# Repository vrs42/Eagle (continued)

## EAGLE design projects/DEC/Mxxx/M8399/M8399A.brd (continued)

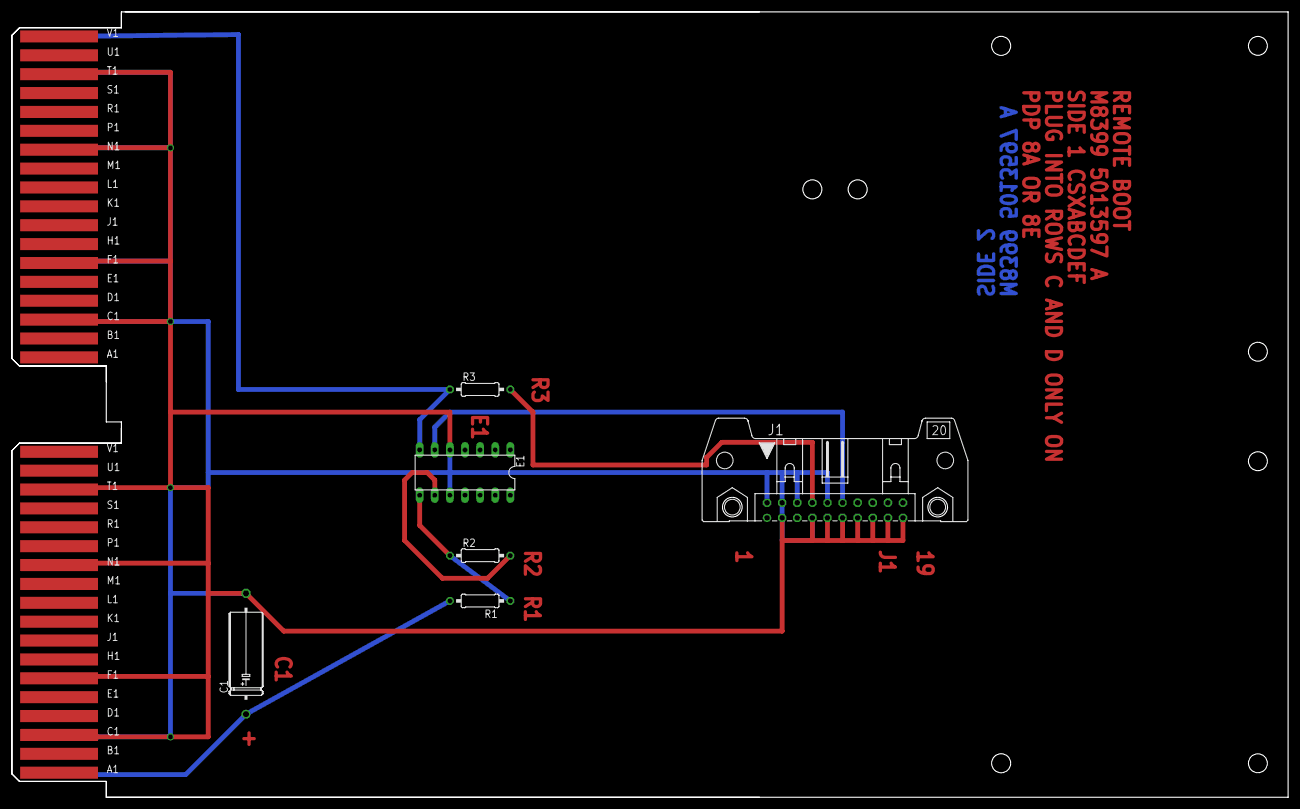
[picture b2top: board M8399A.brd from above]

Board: 2 copper layers, 214.6 x 132.1 mm, 9 parts (0 on the bottom side), 7 nets.

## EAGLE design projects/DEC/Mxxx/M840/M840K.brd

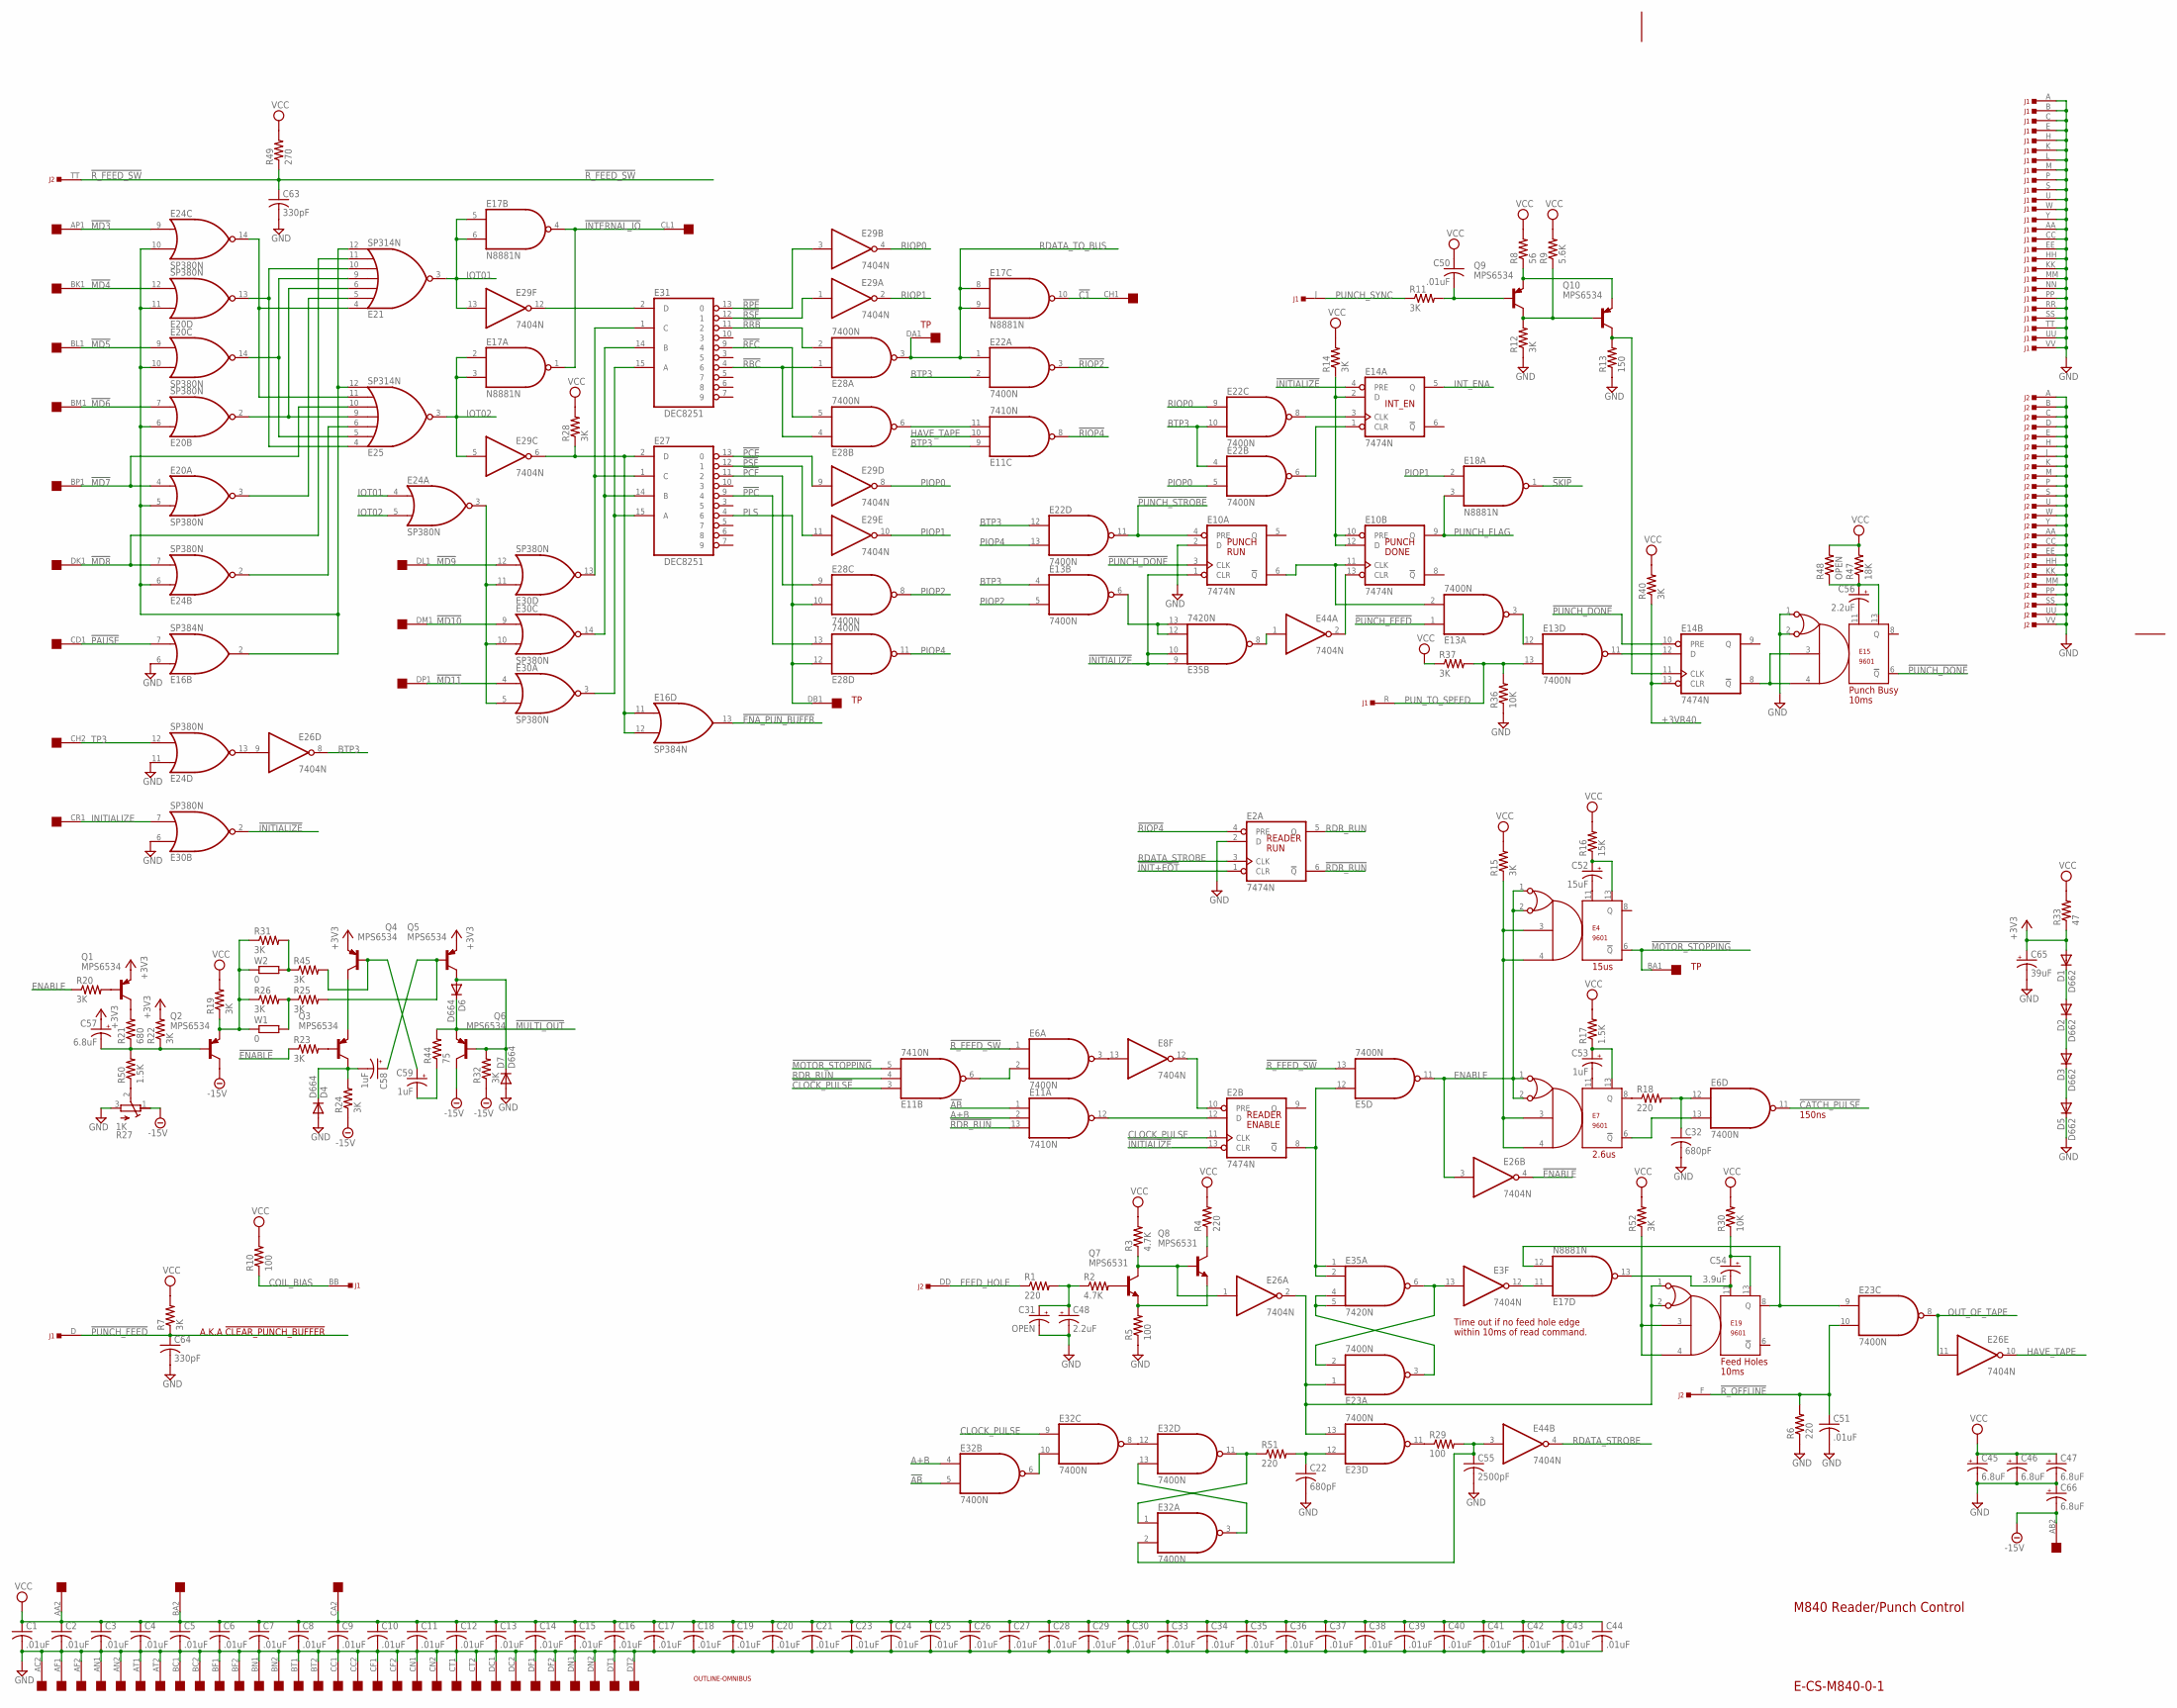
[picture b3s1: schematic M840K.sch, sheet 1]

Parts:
C1, C2, C3, C4, C5, C6, C7, C8, C9, C10, C11, C12, C13, C14, C15, C16, C17, C18, C19, C20, C21, C23, C24, C25, C26, C27, C28, C29, C30, C33, C34, C35, C36, C37, C38, C39, C40, C41, C42, C43, C44: .01uF; C063-025X075
C22, C32: 680pF; C063-025X075
C31: OPEN; E15-5
C45, C46, C47, C57, C66: 6.8uF; E12-8
C48, C56: 2.2uF; E15-5
C50, C51: .01uF; C203-054-229
C52: 15uF; E12-8
C53, C58, C59: 1uF; E15-5
C54: 3.9uF; E15-5
C55: 2500pF; C063-025X075
C63, C64: 330pF; C063-025X075
C65: 39uF; E12-8
D1, D2, D3, D5: D662; DO35-10
D4, D6, D7: D664; DO35-10
E2, E10, E14: 7474N; DIL14
E3, E8, E26, E29, E44: 7404N; DIL14
E4, E7, E15, E19: 9601; DIL14
E5, E6, E13, E22, E23, E28, E32: 7400N; DIL14
E11: 7410N; DIL14
E16: SP384N; DIL14
E17, E18: N8881N; DIL14
E20, E24, E30: SP380N; DIL14
E21, E25: SP314N; DIL14
E27, E31: DEC8251; DIL16
E35: 7420N; DIL14
J1, J2: DEC40PINSH; DEC40PINH
OMNIBUS: QUAD; EDGE-CON8
Q1, Q2, Q3, Q4, Q5, Q6, Q9, Q10: MPS6534; TO5
Q7, Q8: MPS6531; TO5
R1, R4, R6, R18, R51: 220; 0207/10
R2, R3: 4.7K; 0207/10
R5, R10, R29: 100; 0207/10
R7, R11, R12, R14, R15, R19, R20, R22, R23, R24, R25, R26, R28, R31, R32, R37, R40, R45, R52: 3K; 0207/10
R8: 56; 0207/10
R9: 5.6K; 0207/10
R13: 150; 0207/10
R16: 15K; 0207/10
R17, R50: 1.5K; 0207/10
R21: 680; 0207/10
R27: 1K; 3006Y
R30, R36: 10K; 0207/10
R33: 47; 0207/10
R44: 75; 0207/10
R47: 18K; 0207/10
R48: OPEN; 0207/10
R49: 270; 0207/10
U$1: OUTLINE-OMNIBUS; OMNIBUS
W1, W2: 0; 0207/10

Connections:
!AB: E11.1 (I0), E32.5 (I1); also elsewhere on the board
!C1: E17.10 (O), OMNIBUS.CH1
!CATCH_PULSE: E6.11 (O); also elsewhere on the board
!CLOCK_PULSE: E11.3 (I0); also elsewhere on the board
!ENABLE: E26.4 (O), R23.1
!ENA_PUN_BUFFR: E16.13 (O); also elsewhere on the board
!INIT+EOT: E2.1 (CLR); also elsewhere on the board
!INITIALIZE: E2.13 (CLR), E10.1 (CLR), E14.4 (PRE), E30.2 (O), E35.9 (I0), E35.10 (I1); also elsewhere on the board
!INTERNAL_IO: E17.1 (O), E17.4 (O), OMNIBUS.CL1
!IOT: E24.3 (O), E30.5 (I1), E30.10 (I1), E30.11 (I0)
!MD3: E24.9 (I0), OMNIBUS.AP1
!MD4: E20.12 (I1), OMNIBUS.BK1
!MD5: E20.9 (I0), OMNIBUS.BL1
!MD6: E20.7 (I1), OMNIBUS.BM1
!MD7: E20.4 (I0), E25.10 (I4), OMNIBUS.BP1
!MD8: E21.11 (I5), E24.7 (I1), OMNIBUS.DK1
!MD9: E30.12 (I1), OMNIBUS.DL1
!MD10: E30.9 (I0), OMNIBUS.DM1
!MD11: E30.4 (I0), OMNIBUS.DP1
!MOTOR_STOPPING: E4.6 (!Q), E11.5 (I2), OMNIBUS.BA1; also elsewhere on the board
!MULTI_OUT: D6.C, Q6.1 (E), R44.2; also elsewhere on the board
!PAUSE: E16.7 (I1), OMNIBUS.CD1
!PCE: E27.13 (0), E29.9 (I)
!PCF: E27.11 (2), E28.9 (I0)
!PPC: E27.9 (4), E28.13 (I1)
!PSF: E27.12 (1), E29.11 (I)
!PUNCH_DONE: E10.3 (CLK), E14.10 (PRE), E15.6 (!Q); also elsewhere on the board
!PUNCH_FEED: C64.1, E13.1 (I0), J1.D, R7.1; also elsewhere on the board
!PUNCH_STROBE: E10.4 (PRE), E22.11 (O); also elsewhere on the board
!RBC: E28.1 (I0), E28.4 (I0), E31.4 (6)
!RDR_RUN: E2.6 (!Q), E11.13 (I2)
!RFC: E28.5 (I1), E31.9 (4)
!RIOP2: E22.3 (O); also elsewhere on the board
!RIOP4: E2.4 (PRE), E11.8 (O); also elsewhere on the board
!RPE: E29.3 (I), E31.13 (0)
!RRB: E28.2 (I1), E31.11 (2)
!RSF: E29.1 (I), E31.12 (1)
!R_FEED_SW: C63.1, E5.13 (I1), E6.1 (I0), J2.TT, R49.1
!R_OFFLINE: C51.1, E23.10 (I1), J2.F, R6.2
!SKIP: E18.1 (O); also elsewhere on the board
+3V3: C57.+, C65.+, D1.A, Q1.1 (E), Q4.1 (E), Q5.1 (E), R22.2, R33.1
+3VR40: E14.13 (CLR), R40.1; also elsewhere on the board
-15V: C66.-, OMNIBUS.AB2, Q2.3 (C), Q6.3 (C), R24.1, R27.1 (A), R32.1
A+B: E11.2 (I1), E32.4 (I0); also elsewhere on the board
BTP3: E11.9 (I0), E13.4 (I0), E22.2 (I1), E22.4 (I0), E22.10 (I1), E22.12 (I0), E26.8 (O)
CLOCK_PULSE: E2.11 (CLK), E32.9 (I0); also elsewhere on the board
COIL_BIAS: J1.BB, R10.1
ENABLE: E4.1, E4.2, E5.11 (O), E7.1, E7.2, E26.3 (I), R20.1; also elsewhere on the board
FEED_HOLE: J2.DD, R1.1
GND: C1.2, C2.2, C3.2, C4.2, C5.2, C6.2, C7.2, C8.2, C9.2, C10.2, C11.2, C12.2, C13.2, C14.2, C15.2, C16.2, C17.2, C18.2, C19.2, C20.2, C21.2, C22.2, C23.2, C24.2, C25.2, C26.2, C27.2, C28.2, C29.2, C30.2, C31.-, C32.2, C33.2, C34.2, C35.2, C36.2, C37.2, C38.2, C39.2, C40.2, C41.2, C42.2, C43.2, C44.2, C45.-, C46.-, C47.-, C48.-, C51.2, C55.2, C63.2, C64.2, C65.-, C66.+, D4.A, D5.C, D7.A, E2.2 (D), E2.7 (GND), E3.7 (GND), E4.7 (GND), E5.7 (GND), E6.7 (GND), E7.7 (GND), E8.7 (GND), E10.2 (D), E10.7 (GND), E11.7 (GND), E13.7 (GND), E14.7 (GND), E15.1, E15.2, E15.7 (GND), E16.1 (GND), E16.6 (I0), E17.7 (GND), E18.7 (GND), E19.7 (GND), E20.1 (GND), E21.1 (GND), E22.7 (GND), E23.7 (GND), E24.1 (GND), E24.11 (I0), E25.1 (GND), E26.7 (GND), E27.8 (GND), E28.7 (GND), E29.7 (GND), E30.1 (GND), E30.6 (I0), E31.8 (GND), E32.7 (GND), E35.7 (GND), E44.7 (GND), J1.A, J1.AA, J1.B, J1.C, J1.CC, J1.E, J1.EE, J1.H, J1.HH, J1.K, J1.KK, J1.L, J1.M, J1.MM, J1.NN, J1.P, J1.PP, J1.RR, J1.S, J1.SS, J1.TT, J1.U, J1.UU, J1.VV, J1.W, J1.Y, J2.A, J2.AA, J2.B, J2.C, J2.CC, J2.D, J2.E, J2.EE, J2.H, J2.HH, J2.J, J2.K, J2.KK, J2.M, J2.MM, J2.P, J2.PP, J2.S, J2.SS, J2.U, J2.UU, J2.VV, J2.W, J2.Y, OMNIBUS.AC2, OMNIBUS.AF1, OMNIBUS.AF2, OMNIBUS.AN1, OMNIBUS.AN2, OMNIBUS.AT1, OMNIBUS.AT2, OMNIBUS.BC1, OMNIBUS.BC2, OMNIBUS.BF1, OMNIBUS.BF2, OMNIBUS.BN1, OMNIBUS.BN2, OMNIBUS.BT1, OMNIBUS.BT2, OMNIBUS.CC1, OMNIBUS.CC2, OMNIBUS.CF1, OMNIBUS.CF2, OMNIBUS.CN1, OMNIBUS.CN2, OMNIBUS.CT1, OMNIBUS.CT2, OMNIBUS.DC1, OMNIBUS.DC2, OMNIBUS.DF1, OMNIBUS.DF2, OMNIBUS.DN1, OMNIBUS.DN2, OMNIBUS.DT1, OMNIBUS.DT2, R5.1, R6.1, R12.1, R13.1, R27.3 (E), R36.1; also elsewhere on the board
HAVE_TAPE: E11.10 (I1), E26.10 (O)
INITIALIZE: E30.7 (I1), OMNIBUS.CR1
INT_ENA: E14.5 (Q); also elsewhere on the board
IOT01: E17.5 (I0), E17.6 (I1), E21.3 (O), E24.4 (I0), E29.13 (I)
IOT02: E17.2 (I0), E17.3 (I1), E24.5 (I1), E25.3 (O), E29.5 (I)
unnamed: E24.13 (O), E26.9 (I)
unnamed: C31.+, C48.+, R1.2, R2.1
unnamed: Q7.1 (E), Q8.1 (E), R5.2
unnamed: E27.1 (C), E30.13 (O), E31.1 (C)
unnamed: E20.2 (O), E21.6 (I2), E25.9 (I3)
unnamed: E16.2 (O), E20.5 (I1), E20.6 (I0), E20.10 (I1), E20.11 (I0), E21.12 (I6), E24.6 (I0), E24.10 (I1), E25.12 (I6)
unnamed: E26.1 (I), Q7.3 (C), Q8.2 (B), R3.1
unnamed: Q7.2 (B), R2.2
unnamed: Q8.3 (C), R4.1
unnamed: E21.4 (I0), E24.14 (O), E25.11 (I5)
unnamed: Q9.1 (E), Q10.1 (E), R8.1
unnamed: E20.13 (O), E21.10 (I4), E25.4 (I0)
unnamed: C50.2, Q9.2 (B), R11.2
unnamed: E20.14 (O), E21.9 (I3), E25.5 (I1)
unnamed: E24.2 (O), E25.6 (I2)
unnamed: E29.12 (O), E31.2 (D)
unnamed: E20.3 (O), E21.5 (I1)
unnamed: E16.11 (I0), E16.12 (I1), E27.2 (D), E29.6 (O), R28.1
unnamed: E27.14 (B), E30.14 (O), E31.14 (B)
unnamed: E27.15 (A), E30.3 (O), E31.15 (A)
unnamed: Q9.3 (C), Q10.2 (B), R9.1, R12.2
unnamed: E14.11 (CLK), Q10.3 (C), R13.2
unnamed: E11.11 (I2), E28.6 (O)
unnamed: D3.C, D5.A
unnamed: D2.C, D3.A
unnamed: R25.1, R26.2, W1.2
unnamed: D1.C, D2.A
unnamed: Q3.2 (B), R23.2
unnamed: E14.3 (CLK), E22.8 (O)
unnamed: E14.1 (CLR), E22.6 (O)
unnamed: E10.10 (PRE), E10.12 (D), E14.2 (D), R14.1
unnamed: E4.3, E4.4, E7.3, E7.4, R15.1
unnamed: C52.-, E4.11
unnamed: C52.+, E4.13, R16.1
unnamed: C53.-, E7.11
unnamed: C53.+, E7.13, R17.1
unnamed: E7.8 (Q), R18.1
unnamed: C32.1, E6.12 (I0), R18.2
unnamed: E6.13 (I1), E7.6 (!Q)
unnamed: E2.8 (!Q), E5.12 (I0), E35.1 (I0), E35.2 (I1)
unnamed: D6.A, D7.C, Q5.3 (C), Q6.2 (B), R32.2
unnamed: Q1.2 (B), R20.2
unnamed: C54.-, E17.13 (O), E19.11
unnamed: Q1.3 (C), R21.2
unnamed: C57.-, Q2.2 (B), R21.1, R22.1, R50.2
unnamed: R27.2 (S), R50.1
unnamed: Q2.1 (E), R19.1, R26.1, R31.1, W1.1, W2.1
unnamed: R31.2, R45.1, W2.2
unnamed: Q3.1 (E), Q4.3 (C)
unnamed: C54.+, E19.13, R30.1
unnamed: E19.3, E19.4, R52.1
unnamed: C58.+, Q5.2 (B), R25.2
unnamed: C59.+, Q4.2 (B), R45.2
unnamed: C58.-, D4.C, Q3.3 (C), R24.2
unnamed: C59.-, R44.1
unnamed: E19.1, E19.2, E23.1 (I0), E23.13 (I1), E26.2 (O)
unnamed: E17.12 (I1), E19.8 (Q), E23.9 (I0)
unnamed: C22.1, E23.12 (I0), R51.2
unnamed: E3.12 (O), E17.11 (I0)
unnamed: E3.13 (I), E23.2 (I1), E35.6 (O)
unnamed: E23.3 (O), E35.4 (I2), E35.5 (I3)
unnamed: E32.1 (I0), E32.11 (O), R51.1
unnamed: E2.10 (PRE), E8.12 (O)
unnamed: E32.3 (O), E32.13 (I1)
unnamed: E23.11 (O), R29.1
unnamed: C55.1, E32.2 (I1), E44.3 (I), R29.2
unnamed: E32.8 (O), E32.12 (I0)
unnamed: E32.6 (O), E32.10 (I1)
unnamed: E6.3 (O), E8.13 (I)
unnamed: E2.12 (D), E11.12 (O)
unnamed: E13.6 (O), E35.12 (I2), E35.13 (I3)
unnamed: E35.8 (O), E44.1 (I)
unnamed: E10.13 (CLR), E44.2 (O)
unnamed: E6.2 (I1), E11.6 (O)
unnamed: E10.6 (!Q), E10.11 (CLK), E13.2 (I1)
unnamed: E13.3 (O), E13.12 (I0)
unnamed: E13.11 (O), E14.12 (D)
unnamed: E14.8 (!Q), E15.3, E15.4
unnamed: C56.-, E15.11
unnamed: C56.+, E15.13, R47.1, R48.1
OUT_OF_TAPE: E23.8 (O), E26.11 (I); also elsewhere on the board
PIOP0: E22.5 (I1), E29.8 (O)
PIOP1: E18.2 (I0), E29.10 (O)
PIOP2: E13.5 (I1), E28.8 (O)
PIOP4: E22.13 (I1), E28.11 (O)
PLS: E27.4 (6), E28.10 (I1), E28.12 (I0), OMNIBUS.DB1
PUNCH_FLAG: E10.9 (Q), E18.3 (I1); also elsewhere on the board
PUNCH_SYNC: J1.J, R11.1
PUN_TO_SPEED: E13.13 (I1), J1.R, R36.2, R37.2
RDATA_STROBE: E2.3 (CLK), E44.4 (O); also elsewhere on the board
RDATA_TO_BUS: E17.8 (I0), E17.9 (I1), E22.1 (I0), E28.3 (O), OMNIBUS.DA1; also elsewhere on the board
RDR_RUN: E2.5 (Q), E11.4 (I1); also elsewhere on the board
RIOP0: E22.9 (I0), E29.4 (O)
RIOP1: E29.2 (O); also elsewhere on the board
TP3: E24.12 (I1), OMNIBUS.CH2
VCC: C1.1, C2.1, C3.1, C4.1, C5.1, C6.1, C7.1, C8.1, C9.1, C10.1, C11.1, C12.1, C13.1, C14.1, C15.1, C16.1, C17.1, C18.1, C19.1, C20.1, C21.1, C23.1, C24.1, C25.1, C26.1, C27.1, C28.1, C29.1, C30.1, C33.1, C34.1, C35.1, C36.1, C37.1, C38.1, C39.1, C40.1, C41.1, C42.1, C43.1, C44.1, C45.+, C46.+, C47.+, C50.1, E2.14 (VCC), E3.14 (VCC), E4.14 (VCC), E5.14 (VCC), E6.14 (VCC), E7.14 (VCC), E8.14 (VCC), E10.14 (VCC), E11.14 (VCC), E13.14 (VCC), E14.14 (VCC), E15.14 (VCC), E16.8 (VCC), E17.14 (VCC), E18.14 (VCC), E19.14 (VCC), E20.8 (VCC), E21.8 (VCC), E22.14 (VCC), E23.14 (VCC), E24.8 (VCC), E25.8 (VCC), E26.14 (VCC), E27.16 (VCC), E28.14 (VCC), E29.14 (VCC), E30.8 (VCC), E31.16 (VCC), E32.14 (VCC), E35.14 (VCC), E44.14 (VCC), OMNIBUS.AA2, OMNIBUS.BA2, OMNIBUS.CA2, R3.2, R4.2, R7.2, R8.2, R9.2, R10.2, R14.2, R15.2, R16.2, R17.2, R19.2, R28.2, R30.2, R33.2, R37.1, R40.2, R47.2, R48.2, R49.2, R52.2; also elsewhere on the board

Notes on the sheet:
E-CS-M840-0-1
M840 Reader/Punch Control
DONE
INT_EN
Feed Holes
2.6us
15us
150ns
READER
ENABLE
10ms
Time out if no feed hole edge
within 10ms of read command.
PUNCH
RUN
Punch Busy
A.K.A !CLEAR_PUNCH_BUFFER

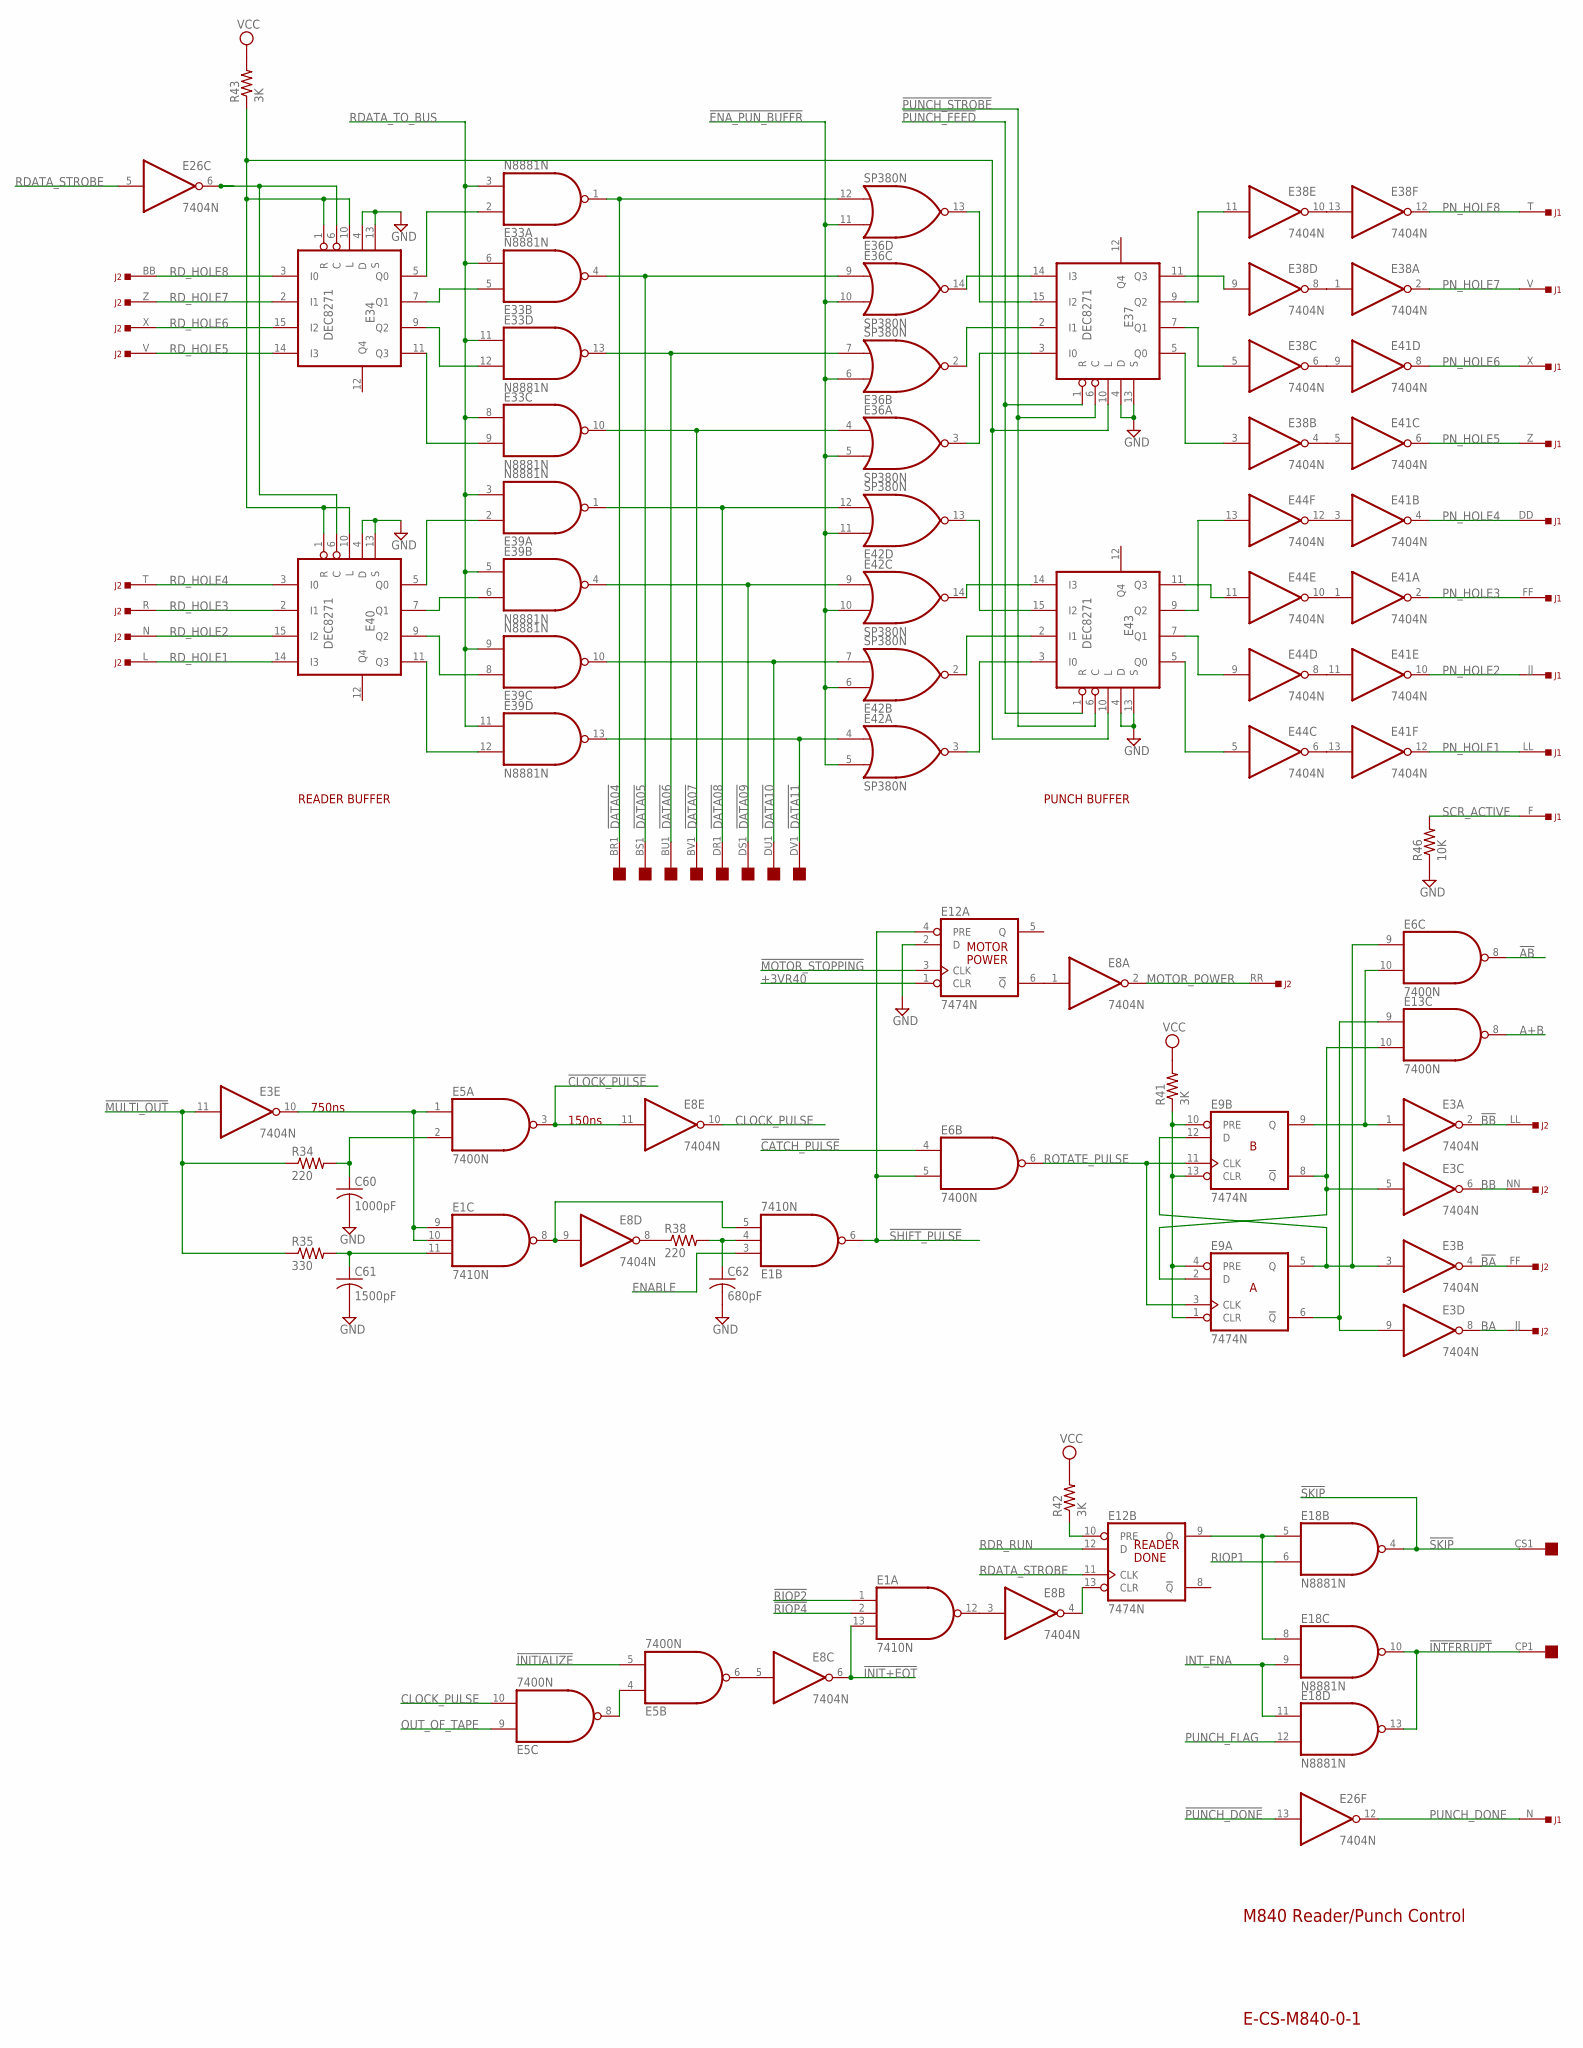
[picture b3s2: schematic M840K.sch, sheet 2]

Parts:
C60: 1000pF; C063-025X075
C61: 1500pF; C063-025X075
C62: 680pF; C063-025X075
E1: 7410N; DIL14
E3, E8, E26, E38, E41, E44: 7404N; DIL14
E5, E6, E13: 7400N; DIL14
E9, E12: 7474N; DIL14
E18, E33, E39: N8881N; DIL14
E34, E37, E40, E43: DEC8271; DIL16
E36, E42: SP380N; DIL14
J1, J2: DEC40PINSH; DEC40PINH
OMNIBUS: QUAD; EDGE-CON8
R34, R38: 220; 0207/10
R35: 330; 0207/10
R41, R42, R43: 3K; 0207/10
R46: 10K; 0207/10

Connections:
!AB: E6.8 (O); also elsewhere on the board
!BA: E3.4 (O), J2.FF
!BB: E3.2 (O), J2.LL
!CATCH_PULSE: E6.4 (I0); also elsewhere on the board
!CLOCK_PULSE: E5.3 (O), E8.11 (I); also elsewhere on the board
!DATA04: E33.1 (O), E36.12 (I1), OMNIBUS.BR1
!DATA05: E33.4 (O), E36.9 (I0), OMNIBUS.BS1
!DATA06: E33.13 (O), E36.7 (I1), OMNIBUS.BU1
!DATA07: E33.10 (O), E36.4 (I0), OMNIBUS.BV1
!DATA08: E39.1 (O), E42.12 (I1), OMNIBUS.DR1
!DATA09: E39.4 (O), E42.9 (I0), OMNIBUS.DS1
!DATA10: E39.10 (O), E42.7 (I1), OMNIBUS.DU1
!DATA11: E39.13 (O), E42.4 (I0), OMNIBUS.DV1
!ENA_PUN_BUFFR: E36.5 (I1), E36.6 (I0), E36.10 (I1), E36.11 (I0), E42.5 (I1), E42.6 (I0), E42.10 (I1), E42.11 (I0); also elsewhere on the board
!INIT+EOT: E1.13 (I2), E8.6 (O); also elsewhere on the board
!INITIALIZE: E5.5 (I1); also elsewhere on the board
!INTERRUPT: E18.10 (O), E18.13 (O), OMNIBUS.CP1
!MOTOR_STOPPING: E12.3 (CLK); also elsewhere on the board
!MULTI_OUT: E3.11 (I), R34.1, R35.1; also elsewhere on the board
!PUNCH_DONE: E26.13 (I); also elsewhere on the board
!PUNCH_FEED: E37.1 (R), E43.1 (R); also elsewhere on the board
!PUNCH_STROBE: E37.6 (C), E43.6 (C); also elsewhere on the board
!RIOP2: E1.1 (I0); also elsewhere on the board
!RIOP4: E1.2 (I1); also elsewhere on the board
!SHIFT_PULSE: E1.6 (O), E6.5 (I1), E12.4 (PRE)
!SKIP: E18.4 (O), OMNIBUS.CS1; also elsewhere on the board
+3VR40: E12.1 (CLR); also elsewhere on the board
A+B: E13.8 (O); also elsewhere on the board
BA: E3.8 (O), J2.JJ
BB: E3.6 (O), J2.NN
CLOCK_PULSE: E5.10 (I1), E8.10 (O); also elsewhere on the board
ENABLE: E1.3 (I0); also elsewhere on the board
GND: C60.2, C61.2, C62.2, E1.7 (GND), E3.7 (GND), E5.7 (GND), E6.7 (GND), E8.7 (GND), E9.7 (GND), E12.2 (D), E12.7 (GND), E13.7 (GND), E18.7 (GND), E26.7 (GND), E33.7 (GND), E34.4 (D), E34.8 (GND), E34.13 (S), E36.1 (GND), E37.4 (D), E37.8 (GND), E37.13 (S), E38.7 (GND), E39.7 (GND), E40.4 (D), E40.8 (GND), E40.13 (S), E41.7 (GND), E42.1 (GND), E43.4 (D), E43.8 (GND), E43.13 (S), E44.7 (GND), R46.1; also elsewhere on the board
INT_ENA: E18.9 (I1), E18.11 (I0); also elsewhere on the board
MOTOR_POWER: E8.2 (O), J2.RR
unnamed: E12.9 (Q), E18.5 (I0), E18.8 (I0)
unnamed: E33.2 (I0), E34.5 (Q0)
unnamed: E33.5 (I0), E34.7 (Q1)
unnamed: E33.12 (I1), E34.9 (Q2)
unnamed: E33.9 (I1), E34.11 (Q3)
unnamed: E39.2 (I0), E40.5 (Q0)
unnamed: E39.6 (I1), E40.7 (Q1)
unnamed: E39.8 (I0), E40.9 (Q2)
unnamed: E39.12 (I1), E40.11 (Q3)
unnamed: E12.10 (PRE), R42.1
unnamed: E34.1 (R), E34.10 (L), E37.10 (L), E40.1 (R), E40.10 (L), E43.10 (L), R43.1
unnamed: E5.4 (I0), E5.8 (O)
unnamed: E42.3 (O), E43.3 (I0)
unnamed: E26.6 (O), E34.6 (C), E40.6 (C)
unnamed: E42.2 (O), E43.2 (I1)
unnamed: E42.14 (O), E43.14 (I3)
unnamed: E42.13 (O), E43.15 (I2)
unnamed: E36.13 (O), E37.15 (I2)
unnamed: E36.14 (O), E37.14 (I3)
unnamed: E36.2 (O), E37.2 (I1)
unnamed: E3.5 (I), E9.2 (D), E9.8 (!Q), E13.10 (I1)
unnamed: E3.1 (I), E6.10 (I1), E9.9 (Q)
unnamed: E3.3 (I), E6.9 (I0), E9.5 (Q), E9.12 (D)
unnamed: E36.3 (O), E37.3 (I0)
unnamed: E8.4 (O), E12.13 (CLR)
unnamed: E38.10 (O), E38.13 (I)
unnamed: E38.1 (I), E38.8 (O)
unnamed: E38.6 (O), E41.9 (I)
unnamed: E38.4 (O), E41.5 (I)
unnamed: E37.5 (Q0), E38.3 (I)
unnamed: E37.7 (Q1), E38.5 (I)
unnamed: E37.9 (Q2), E38.11 (I)
unnamed: E37.11 (Q3), E38.9 (I)
unnamed: E43.5 (Q0), E44.5 (I)
unnamed: E43.9 (Q2), E44.13 (I)
unnamed: E43.11 (Q3), E44.11 (I)
unnamed: E43.7 (Q1), E44.9 (I)
unnamed: E41.3 (I), E44.12 (O)
unnamed: E41.1 (I), E44.10 (O)
unnamed: E41.11 (I), E44.8 (O)
unnamed: E41.13 (I), E44.6 (O)
unnamed: E3.9 (I), E9.6 (!Q), E13.9 (I0)
unnamed: E9.1 (CLR), E9.4 (PRE), E9.10 (PRE), E9.13 (CLR), R41.1
unnamed: E1.9 (I0), E1.10 (I1), E3.10 (O), E5.1 (I0)
unnamed: C62.1, E1.4 (I1), R38.2
unnamed: E8.8 (O), R38.1
unnamed: E1.5 (I2), E1.8 (O), E8.9 (I)
unnamed: C61.1, E1.11 (I2), R35.2
unnamed: C60.1, E5.2 (I1), R34.2
unnamed: E8.1 (I), E12.6 (!Q)
unnamed: E1.12 (O), E8.3 (I)
unnamed: E5.6 (O), E8.5 (I)
OUT_OF_TAPE: E5.9 (I0); also elsewhere on the board
PN_HOLE1: E41.12 (O), J1.LL
PN_HOLE2: E41.10 (O), J1.JJ
PN_HOLE3: E41.2 (O), J1.FF
PN_HOLE4: E41.4 (O), J1.DD
PN_HOLE5: E41.6 (O), J1.Z
PN_HOLE6: E41.8 (O), J1.X
PN_HOLE7: E38.2 (O), J1.V
PN_HOLE8: E38.12 (O), J1.T
PUNCH_DONE: E26.12 (O), J1.N
PUNCH_FLAG: E18.12 (I1); also elsewhere on the board
RDATA_STROBE: E12.11 (CLK), E26.5 (I); also elsewhere on the board
RDATA_TO_BUS: E33.3 (I1), E33.6 (I1), E33.8 (I0), E33.11 (I0), E39.3 (I1), E39.5 (I0), E39.9 (I1), E39.11 (I0); also elsewhere on the board
RDR_RUN: E12.12 (D); also elsewhere on the board
RD_HOLE1: E40.14 (I3), J2.L
RD_HOLE2: E40.15 (I2), J2.N
RD_HOLE3: E40.2 (I1), J2.R
RD_HOLE4: E40.3 (I0), J2.T
RD_HOLE5: E34.14 (I3), J2.V
RD_HOLE6: E34.15 (I2), J2.X
RD_HOLE7: E34.2 (I1), J2.Z
RD_HOLE8: E34.3 (I0), J2.BB
RIOP1: E18.6 (I1); also elsewhere on the board
ROTATE_PULSE: E6.6 (O), E9.3 (CLK), E9.11 (CLK)
SCR_ACTIVE: J1.F, R46.2
VCC: E1.14 (VCC), E3.14 (VCC), E5.14 (VCC), E6.14 (VCC), E8.14 (VCC), E9.14 (VCC), E12.14 (VCC), E13.14 (VCC), E18.14 (VCC), E26.14 (VCC), E33.14 (VCC), E34.16 (VCC), E36.8 (VCC), E37.16 (VCC), E38.14 (VCC), E39.14 (VCC), E40.16 (VCC), E41.14 (VCC), E42.8 (VCC), E43.16 (VCC), E44.14 (VCC), R41.2, R42.2, R43.2; also elsewhere on the board

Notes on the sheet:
E-CS-M840-0-1
M840 Reader/Punch Control
PUNCH BUFFER
READER BUFFER
MOTOR
POWER
750ns
150ns
READER
DONE

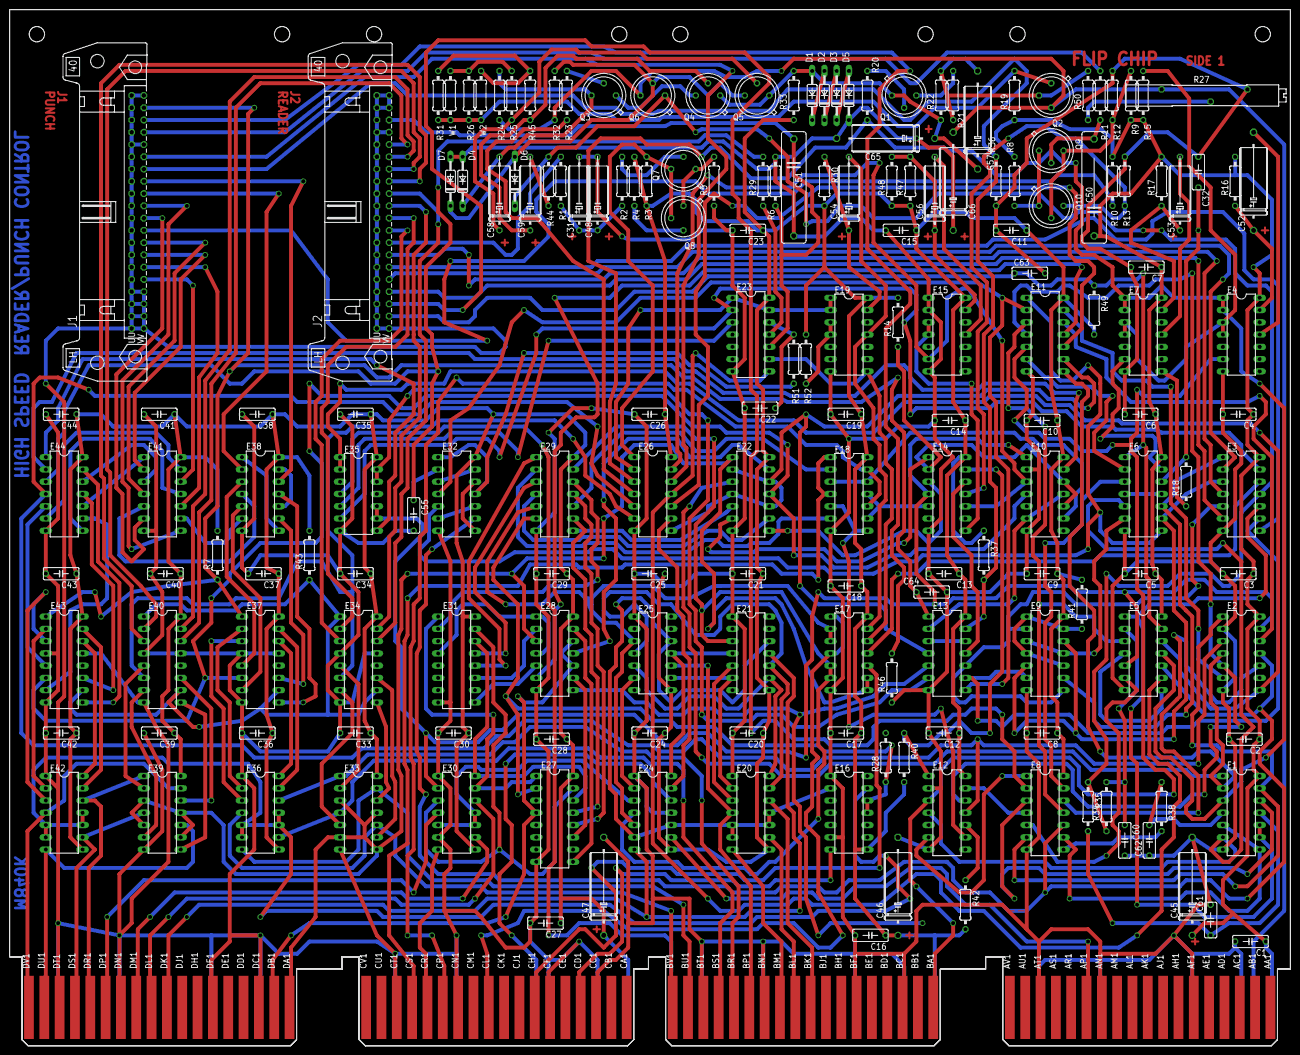
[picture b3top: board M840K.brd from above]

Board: 4 copper layers, 265.3 x 214.6 mm, 183 parts (0 on the bottom side), 237 nets.
